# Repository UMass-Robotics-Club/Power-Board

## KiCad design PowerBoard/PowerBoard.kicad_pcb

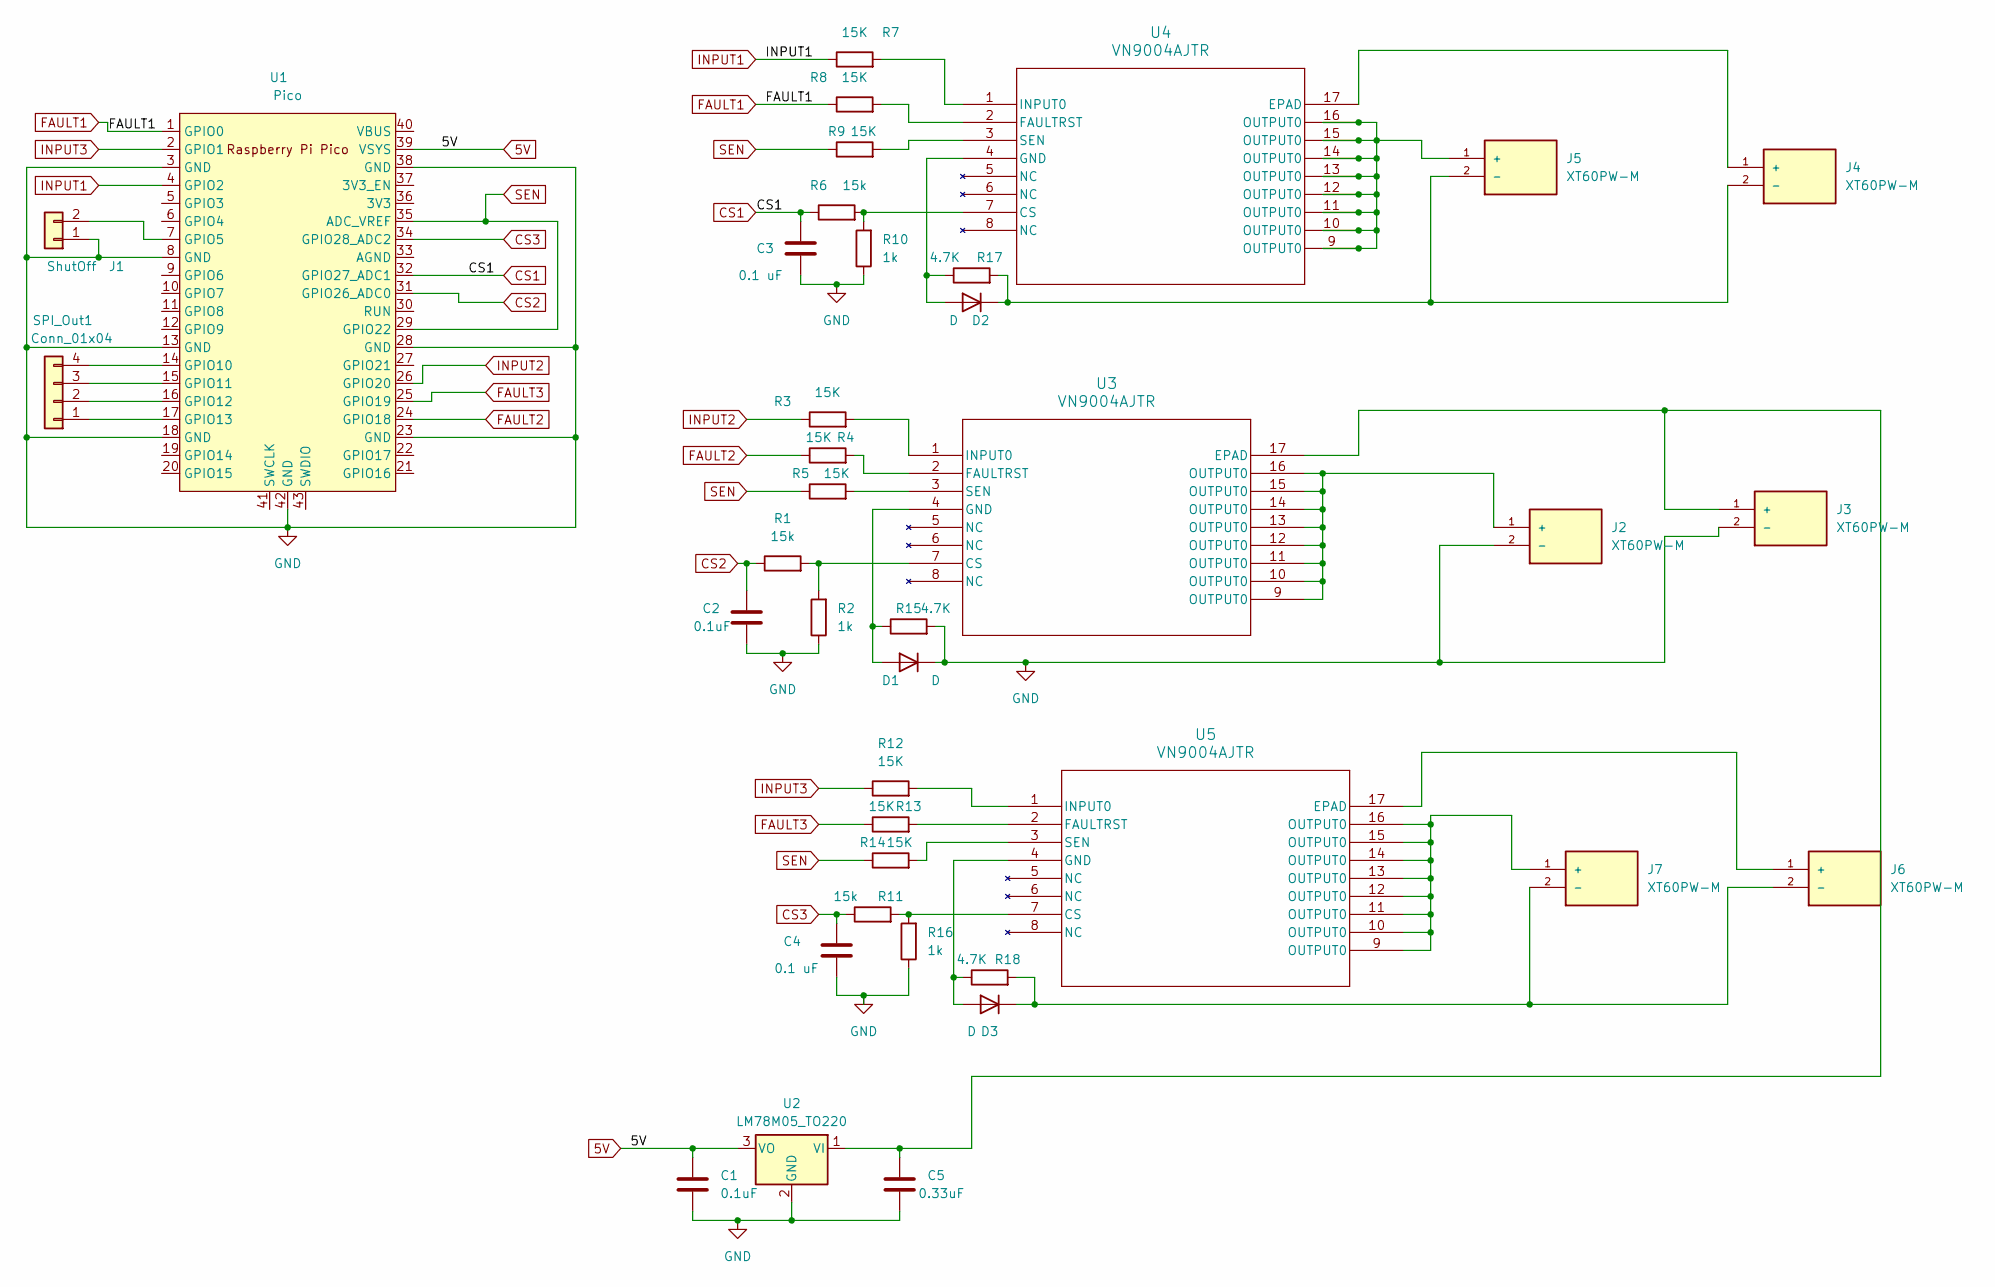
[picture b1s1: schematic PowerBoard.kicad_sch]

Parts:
C1: 0.1uF; C_Disc_D5.0mm_W2.5mm_P5.00mm
C2: 0.1uF; C_Disc_D5.1mm_W3.2mm_P5.00mm
C3, C4: 0.1 uF; C_Disc_D5.1mm_W3.2mm_P5.00mm
C5: 0.33uF; C_Disc_D5.0mm_W2.5mm_P5.00mm
D1, D2, D3: D; D_DO-41_SOD81_P7.62mm_Horizontal
J1: ShutOff; PinHeader_1x02_P2.54mm_Vertical
J2, J3, J4, J5, J6, J7: XT60PW-M; AMASS_XT60PW-M_1x02_P7.20mm_Horizontal; PARTREV V1.2
R1, R6, R11: 15k; R_0603_1608Metric_Pad0.98x0.95mm_HandSolder
R2, R10, R16: 1k; R_Axial_DIN0207_L6.3mm_D2.5mm_P7.62mm_Horizontal
R3, R4, R5, R7, R8, R9, R12, R13, R14: 15K; R_0603_1608Metric_Pad0.98x0.95mm_HandSolder
R15, R17, R18: 4.7K; R_Axial_DIN0207_L6.3mm_D2.5mm_P7.62mm_Horizontal
SPI_Out1: Conn_01x04; PinHeader_1x04_P2.54mm_Vertical
U1: Pico; RPi_Pico_SMD_TH
U2: LM78M05_TO220; TO-220-3_Vertical
U3, U4, U5: VN9004AJTR; POWERSSO16_VN9004_STM-L

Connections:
5V: C1.1, U1.39 (VSYS), U2.3 (VO)
CS1: C3.1, R6.1, U1.32 (GPIO27_ADC1)
CS2: C2.1, R1.1, U1.31 (GPIO26_ADC0)
CS3: C4.1, R11.1, U1.34 (GPIO28_ADC2)
FAULT1: R8.1, U1.1 (GPIO0)
FAULT2: R4.1, U1.24 (GPIO18)
FAULT3: R13.1, U1.25 (GPIO19)
GND: C1.2, C2.2, C3.2, C4.2, C5.2, D1.1 (K), J1.1, J2.2 (-), J3.2 (-), R2.1, R10.1, R15.2, R16.1, U1.3 (GND), U1.8 (GND), U1.13 (GND), U1.18 (GND), U1.23 (GND), U1.28 (GND), U1.38 (GND), U1.42 (GND), U2.2 (GND)
INPUT1: R7.1, U1.4 (GPIO2)
INPUT2: R3.1, U1.26 (GPIO20)
INPUT3: R12.1, U1.2 (GPIO1)
unnamed: D1.2 (A), R15.1, U3.4 (GND)
unnamed: D2.2 (A), R17.1, U4.4 (GND)
unnamed: D2.1 (K), J4.2 (-), J5.2 (-), R17.2
unnamed: D3.2 (A), R18.1, U5.4 (GND)
unnamed: D3.1 (K), J6.2 (-), J7.2 (-), R18.2
unnamed: J1.2, U1.7 (GPIO5)
unnamed: J2.1 (+), U3.9 (OUTPUT0), U3.10 (OUTPUT0), U3.11 (OUTPUT0), U3.12 (OUTPUT0), U3.13 (OUTPUT0), U3.14 (OUTPUT0), U3.15 (OUTPUT0), U3.16 (OUTPUT0)
unnamed: C5.1, J3.1 (+), U2.1 (VI), U3.17 (EPAD)
unnamed: J4.1 (+), U4.17 (EPAD)
unnamed: J5.1 (+), U4.9 (OUTPUT0), U4.10 (OUTPUT0), U4.11 (OUTPUT0), U4.12 (OUTPUT0), U4.13 (OUTPUT0), U4.14 (OUTPUT0), U4.15 (OUTPUT0), U4.16 (OUTPUT0)
unnamed: J6.1 (+), U5.17 (EPAD)
unnamed: J7.1 (+), U5.9 (OUTPUT0), U5.10 (OUTPUT0), U5.11 (OUTPUT0), U5.12 (OUTPUT0), U5.13 (OUTPUT0), U5.14 (OUTPUT0), U5.15 (OUTPUT0), U5.16 (OUTPUT0)
unnamed: SPI_Out1.1, U1.17 (GPIO13)
unnamed: SPI_Out1.2, U1.16 (GPIO12)
unnamed: SPI_Out1.3, U1.15 (GPIO11)
unnamed: SPI_Out1.4, U1.14 (GPIO10)
unnamed: R1.2, R2.2, U3.7 (CS)
unnamed: R4.2, U3.2 (FAULTRST)
unnamed: R3.2, U3.1 (INPUT0)
unnamed: R5.2, U3.3 (SEN)
unnamed: R6.2, R10.2, U4.7 (CS)
unnamed: R8.2, U4.2 (FAULTRST)
unnamed: R7.2, U4.1 (INPUT0)
unnamed: R9.2, U4.3 (SEN)
unnamed: R11.2, R16.2, U5.7 (CS)
unnamed: R13.2, U5.2 (FAULTRST)
unnamed: R12.2, U5.1 (INPUT0)
unnamed: R14.2, U5.3 (SEN)
SEN: R5.1, R9.1, R14.1, U1.29 (GPIO22), U1.35 (ADC_VREF)

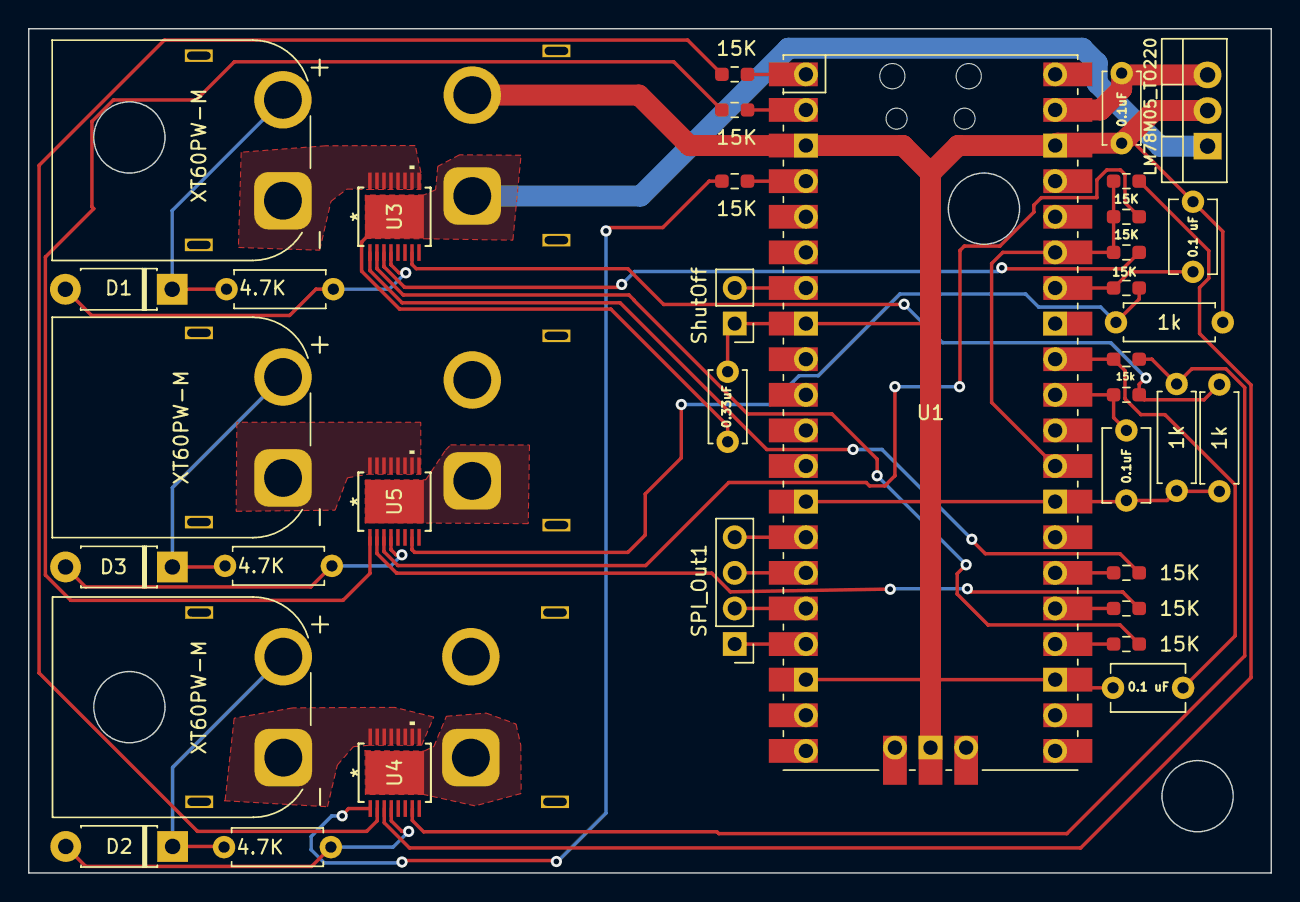
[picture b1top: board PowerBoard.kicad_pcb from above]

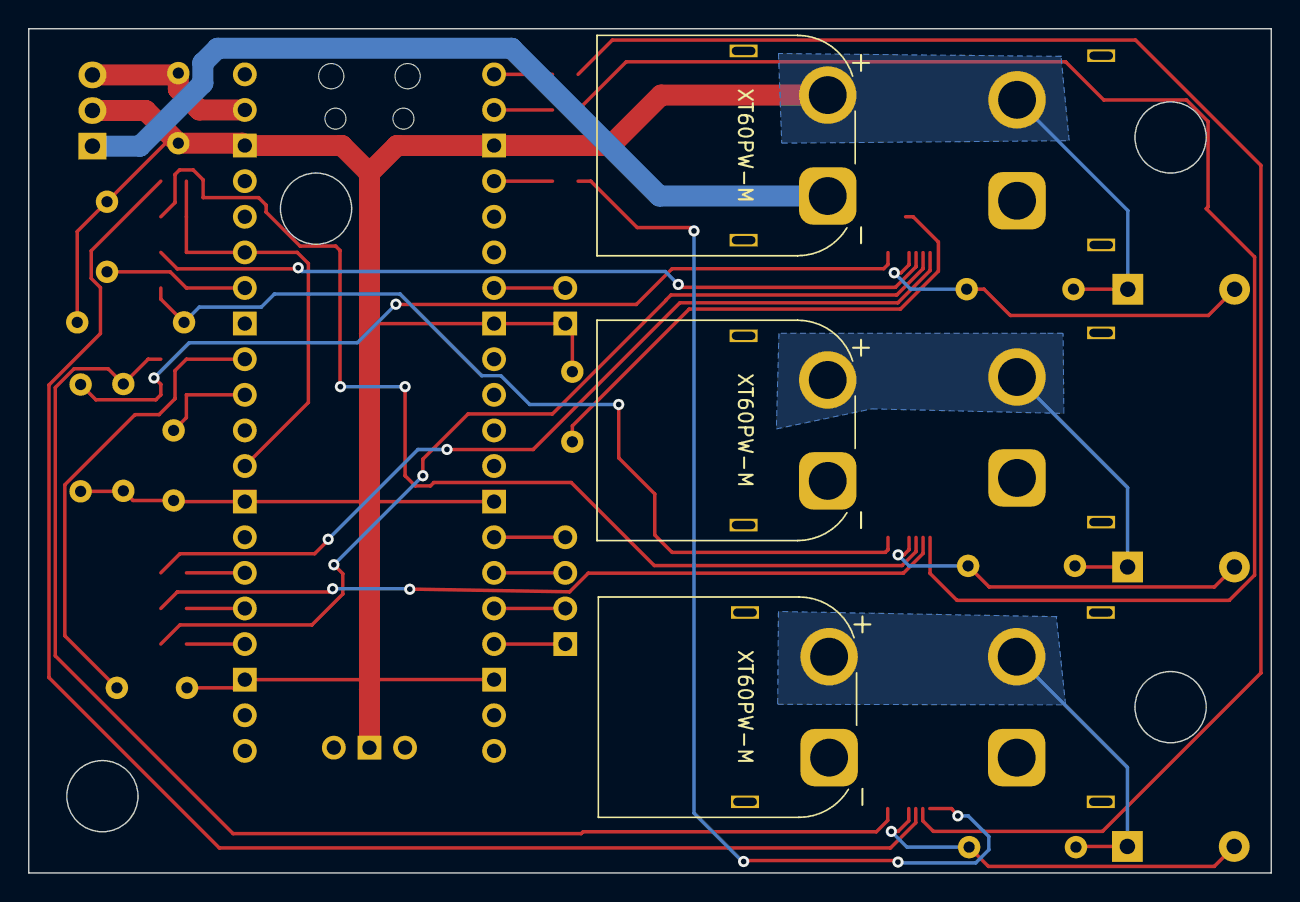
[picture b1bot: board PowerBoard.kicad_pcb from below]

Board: 2 copper layers, 88.6 x 60.2 mm, 39 parts (3 on the bottom side), 40 nets.

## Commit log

2025-02-21 Inital Creation
